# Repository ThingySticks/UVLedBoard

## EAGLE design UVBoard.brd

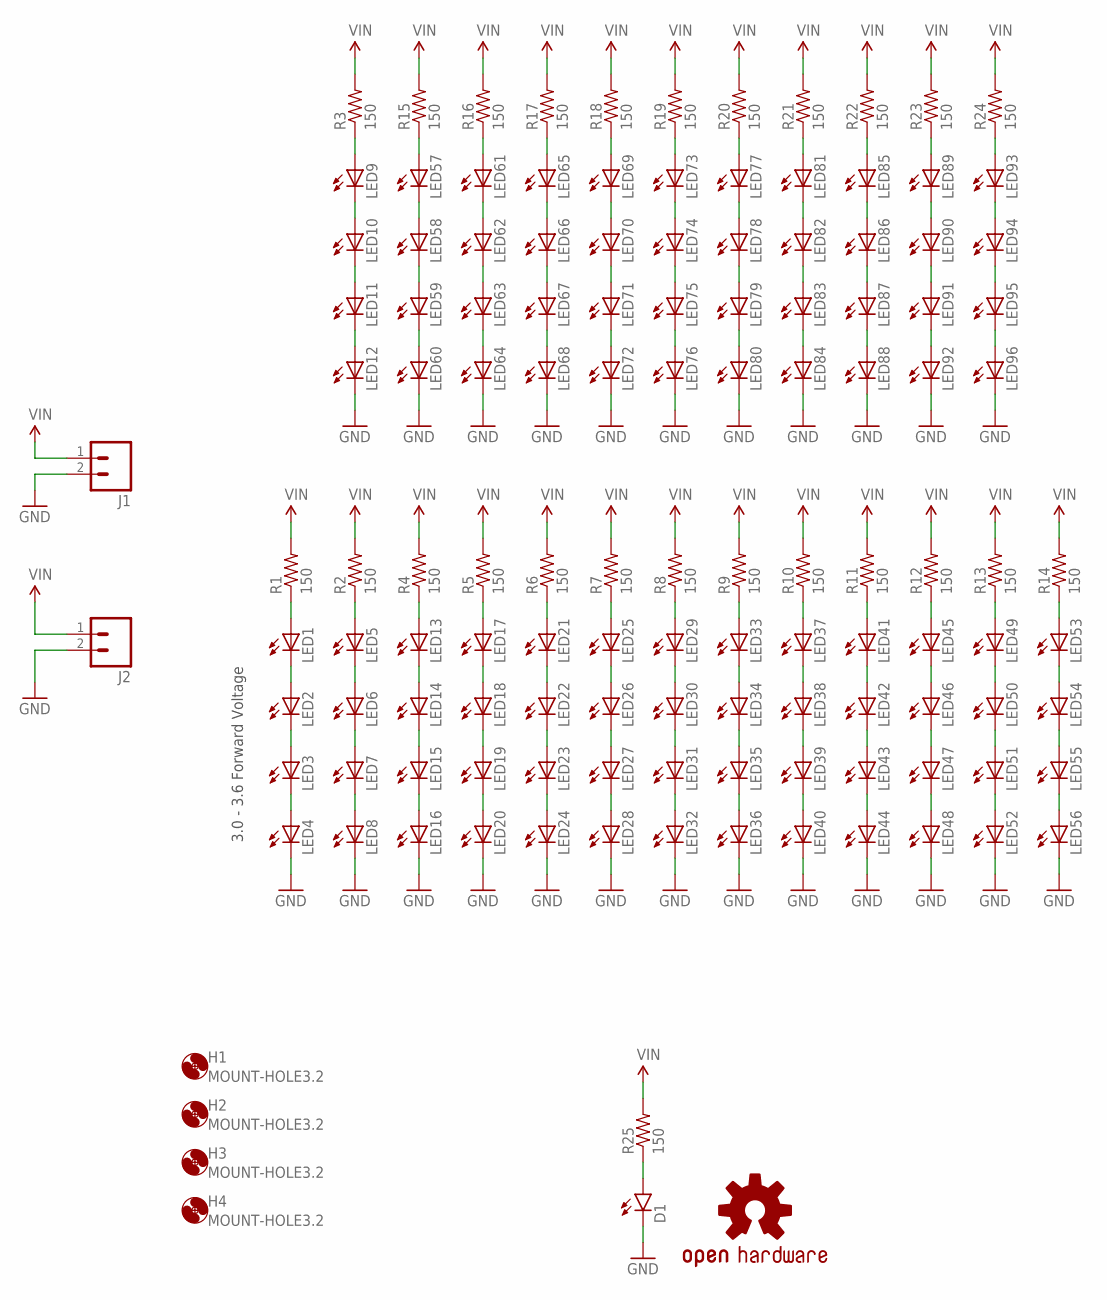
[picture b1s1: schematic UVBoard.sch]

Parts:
D1: LED1206-BOTTOM; LED-1206-BOTTOM
H1, H2, H3, H4: MOUNT-HOLE3.2; 3,2
J1, J2: M023.5MM; SCREWTERMINAL-3.5MM-2
LED1, LED2, LED3, LED4, LED5, LED6, LED7, LED8, LED9, LED10, LED11, LED12, LED13, LED14, LED15, LED16, LED17, LED18, LED19, LED20, LED21, LED22, LED23, LED24, LED25, LED26, LED27, LED28, LED29, LED30, LED31, LED32, LED33, LED34, LED35, LED36, LED37, LED38, LED39, LED40, LED41, LED42, LED43, LED44, LED45, LED46, LED47, LED48, LED49, LED50, LED51, LED52, LED53, LED54, LED55, LED56, LED57, LED58, LED59, LED60, LED61, LED62, LED63, LED64, LED65, LED66, LED67, LED68, LED69, LED70, LED71, LED72, LED73, LED74, LED75, LED76, LED77, LED78, LED79, LED80, LED81, LED82, LED83, LED84, LED85, LED86, LED87, LED88, LED89, LED90, LED91, LED92, LED93, LED94, LED95, LED96: LEDP-LCC-2; P-LCC-2
LOGO1: OSHW-LOGOM; OSHW-LOGO-M
R1, R2, R3, R4, R5, R6, R7, R8, R9, R10, R11, R12, R13, R14, R15, R16, R17, R18, R19, R20, R21, R22, R23, R24, R25: 150; 1206

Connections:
GND: D1.C, J1.2, J2.2, LED4.C, LED8.C, LED12.C, LED16.C, LED20.C, LED24.C, LED28.C, LED32.C, LED36.C, LED40.C, LED44.C, LED48.C, LED52.C, LED56.C, LED60.C, LED64.C, LED68.C, LED72.C, LED76.C, LED80.C, LED84.C, LED88.C, LED92.C, LED96.C
unnamed: LED1.C, LED2.A
unnamed: LED2.C, LED3.A
unnamed: LED3.C, LED4.A
unnamed: LED1.A, R1.1
unnamed: LED5.C, LED6.A
unnamed: LED6.C, LED7.A
unnamed: LED7.C, LED8.A
unnamed: LED5.A, R2.1
unnamed: LED9.C, LED10.A
unnamed: LED10.C, LED11.A
unnamed: LED11.C, LED12.A
unnamed: LED9.A, R3.1
unnamed: LED13.C, LED14.A
unnamed: LED14.C, LED15.A
unnamed: LED15.C, LED16.A
unnamed: LED13.A, R4.1
unnamed: LED17.C, LED18.A
unnamed: LED18.C, LED19.A
unnamed: LED19.C, LED20.A
unnamed: LED17.A, R5.1
unnamed: LED21.C, LED22.A
unnamed: LED22.C, LED23.A
unnamed: LED23.C, LED24.A
unnamed: LED21.A, R6.1
unnamed: LED25.C, LED26.A
unnamed: LED26.C, LED27.A
unnamed: LED27.C, LED28.A
unnamed: LED25.A, R7.1
unnamed: LED29.C, LED30.A
unnamed: LED30.C, LED31.A
unnamed: LED31.C, LED32.A
unnamed: LED29.A, R8.1
unnamed: LED33.C, LED34.A
unnamed: LED34.C, LED35.A
unnamed: LED35.C, LED36.A
unnamed: LED33.A, R9.1
unnamed: LED37.C, LED38.A
unnamed: LED38.C, LED39.A
unnamed: LED39.C, LED40.A
unnamed: LED37.A, R10.1
unnamed: LED41.C, LED42.A
unnamed: LED42.C, LED43.A
unnamed: LED43.C, LED44.A
unnamed: LED41.A, R11.1
unnamed: LED45.C, LED46.A
unnamed: LED46.C, LED47.A
unnamed: LED47.C, LED48.A
unnamed: LED45.A, R12.1
unnamed: LED49.C, LED50.A
unnamed: LED50.C, LED51.A
unnamed: LED51.C, LED52.A
unnamed: LED49.A, R13.1
unnamed: LED53.C, LED54.A
unnamed: LED54.C, LED55.A
unnamed: LED55.C, LED56.A
unnamed: LED53.A, R14.1
unnamed: LED57.C, LED58.A
unnamed: LED58.C, LED59.A
unnamed: LED59.C, LED60.A
unnamed: LED57.A, R15.1
unnamed: LED61.C, LED62.A
unnamed: LED62.C, LED63.A
unnamed: LED63.C, LED64.A
unnamed: LED61.A, R16.1
unnamed: LED65.C, LED66.A
unnamed: LED66.C, LED67.A
unnamed: LED67.C, LED68.A
unnamed: LED65.A, R17.1
unnamed: LED69.C, LED70.A
unnamed: LED70.C, LED71.A
unnamed: LED71.C, LED72.A
unnamed: LED69.A, R18.1
unnamed: LED73.C, LED74.A
unnamed: LED74.C, LED75.A
unnamed: LED75.C, LED76.A
unnamed: LED73.A, R19.1
unnamed: LED77.C, LED78.A
unnamed: LED78.C, LED79.A
unnamed: LED79.C, LED80.A
unnamed: LED77.A, R20.1
unnamed: LED81.C, LED82.A
unnamed: LED82.C, LED83.A
unnamed: LED83.C, LED84.A
unnamed: LED81.A, R21.1
unnamed: LED85.C, LED86.A
unnamed: LED86.C, LED87.A
unnamed: LED87.C, LED88.A
unnamed: LED85.A, R22.1
unnamed: LED89.C, LED90.A
unnamed: LED90.C, LED91.A
unnamed: LED91.C, LED92.A
unnamed: LED89.A, R23.1
unnamed: LED93.C, LED94.A
unnamed: LED94.C, LED95.A
unnamed: LED95.C, LED96.A
unnamed: LED93.A, R24.1
unnamed: D1.A, R25.1
VIN: J1.1, J2.1, R1.2, R2.2, R3.2, R4.2, R5.2, R6.2, R7.2, R8.2, R9.2, R10.2, R11.2, R12.2, R13.2, R14.2, R15.2, R16.2, R17.2, R18.2, R19.2, R20.2, R21.2, R22.2, R23.2, R24.2, R25.2

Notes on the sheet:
3.0 - 3.6 Forward Voltage

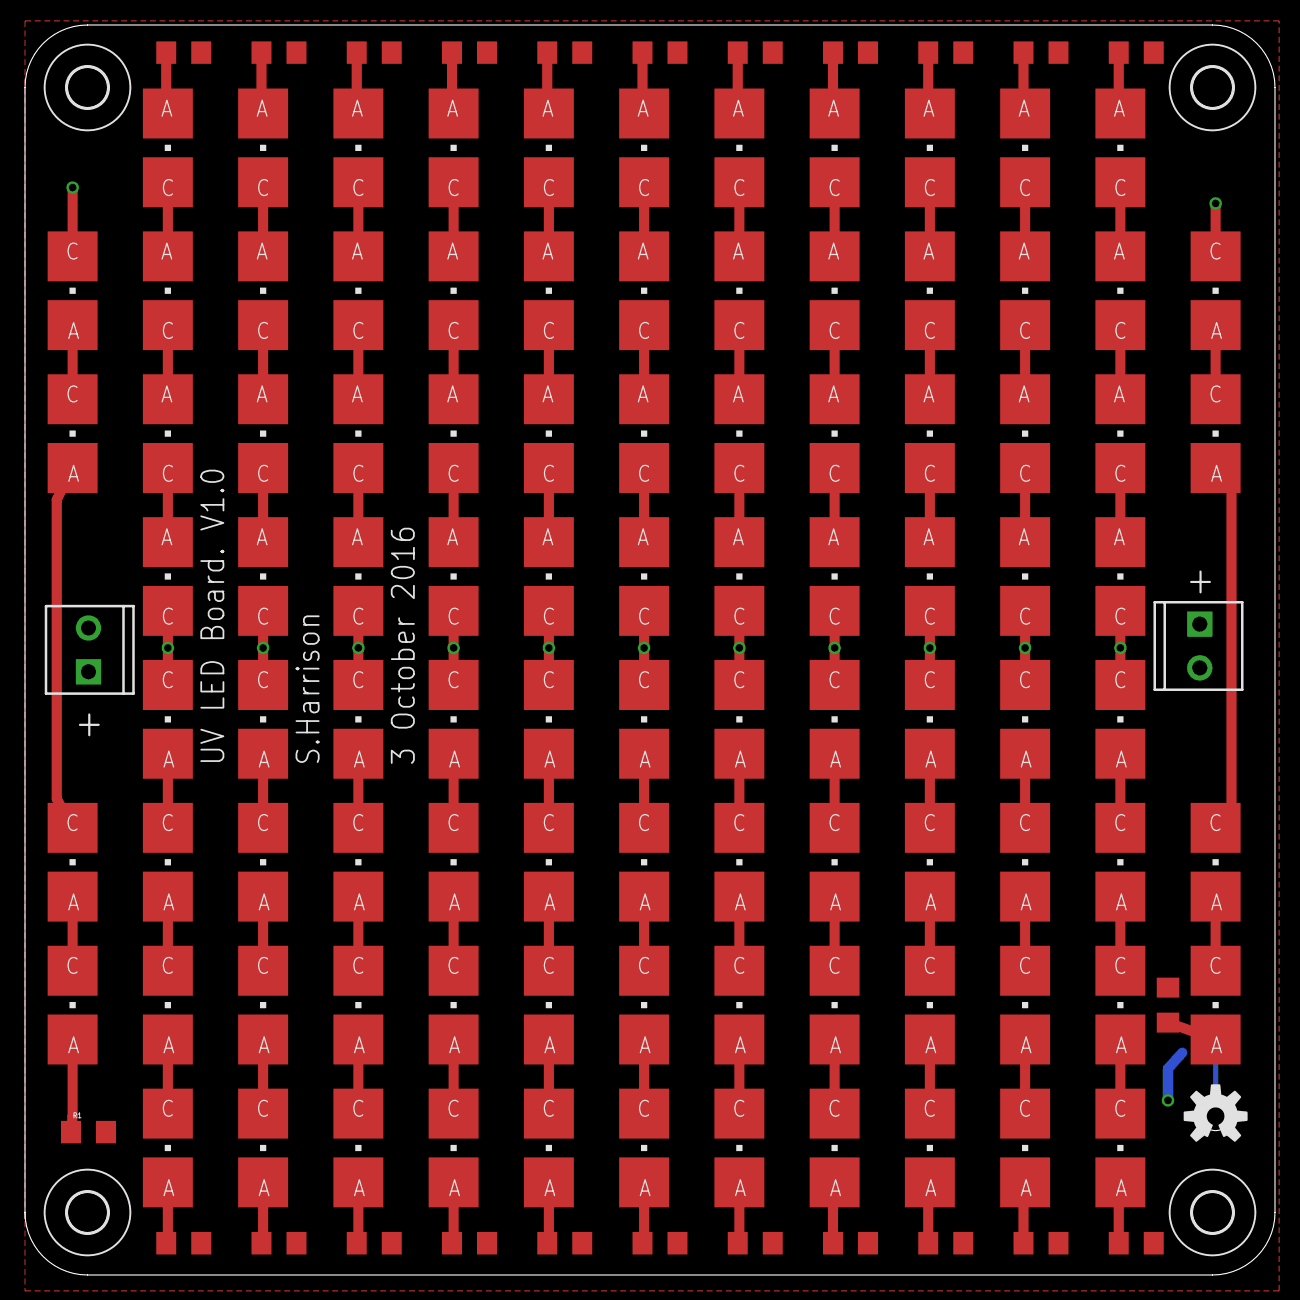
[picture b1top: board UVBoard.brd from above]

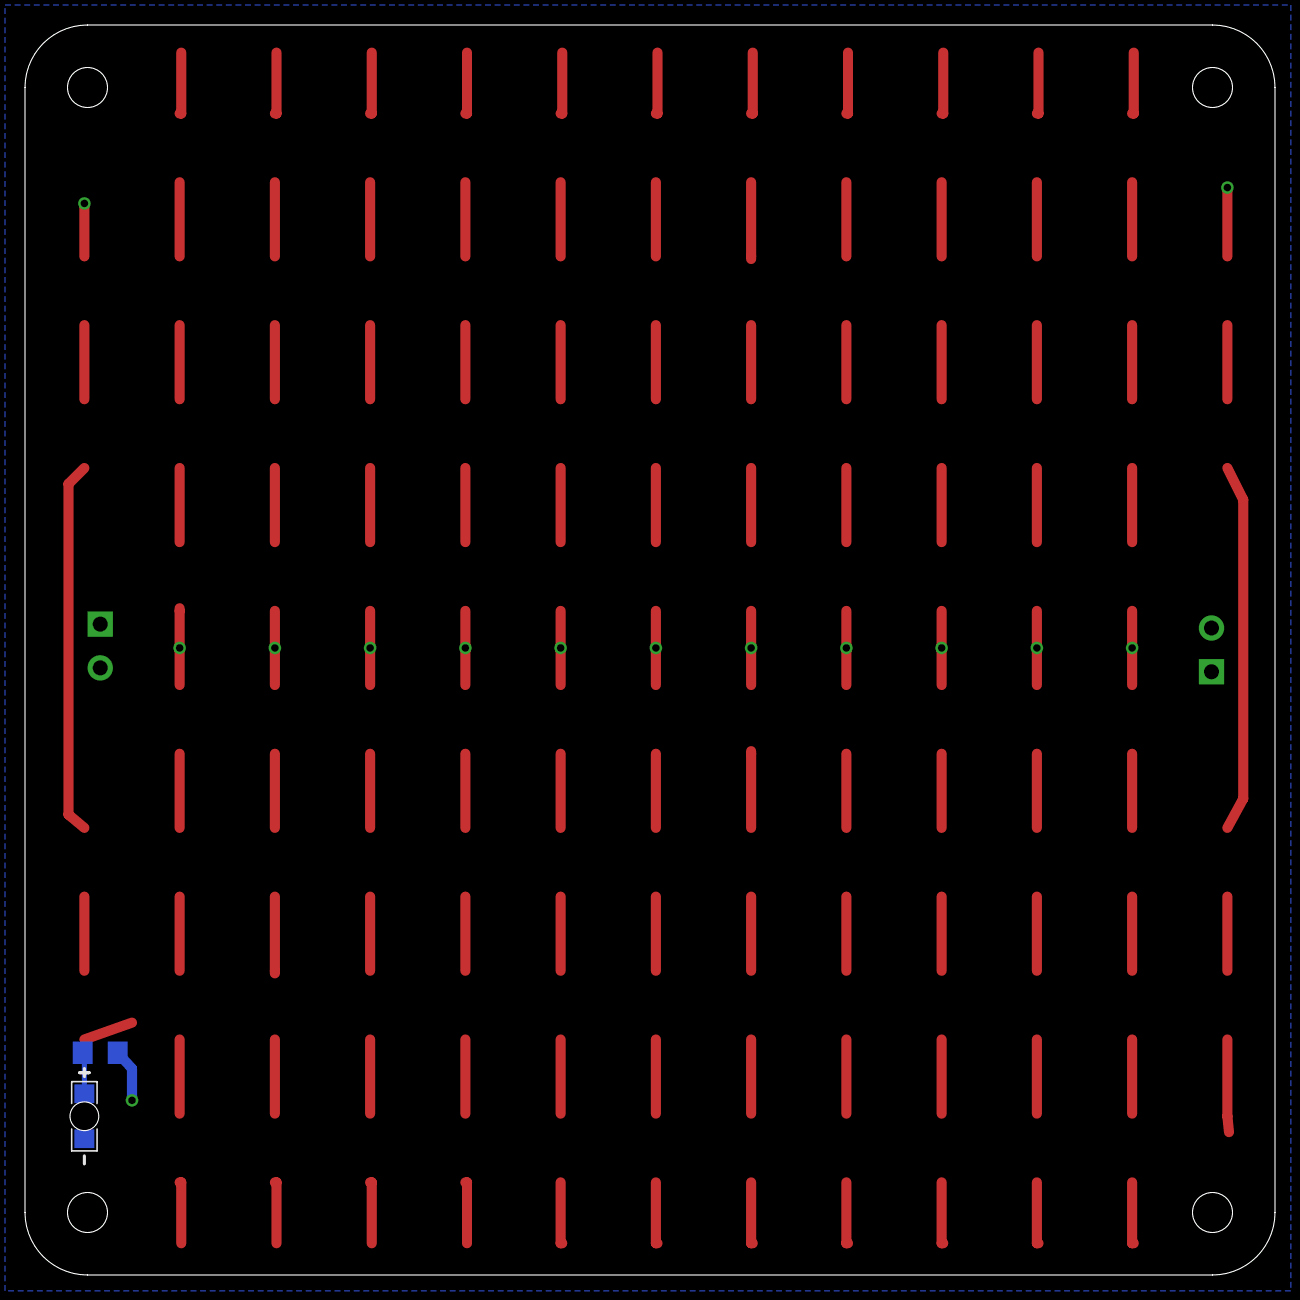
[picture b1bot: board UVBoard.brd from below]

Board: 2 copper layers, 100.0 x 100.0 mm, 129 parts (2 on the bottom side), 99 nets.

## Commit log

2017-01-03 Adding first version of PCB.

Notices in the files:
parts and their libraries:
SparkFun-Passives: Licensing: Creative Commons ShareAlike 4.0 International - https://creativecommons.org/licenses/by-sa/4.0
